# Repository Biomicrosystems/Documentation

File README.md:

# Logos
- The Logo of our group, and all of its versions, has been developed by Designer and Electronic Engineer Gina Paola Salazar

# Figures for papers, presentations, thesis and posters
- All figures of equipment and microsystems were produced by Designer Maria Alejandra Mariño 

When using these images please acknowledge respectively

# File Formats
- LABBOOK: The Excel file format of our groups to document your experimental data
- Confidential Agreement (NDA): document to sign the confidential agreement of the group (spanish version)
- Poster: Our group's powerpoint format for posters
- Presentation: Our group's powerpoint format for presentations

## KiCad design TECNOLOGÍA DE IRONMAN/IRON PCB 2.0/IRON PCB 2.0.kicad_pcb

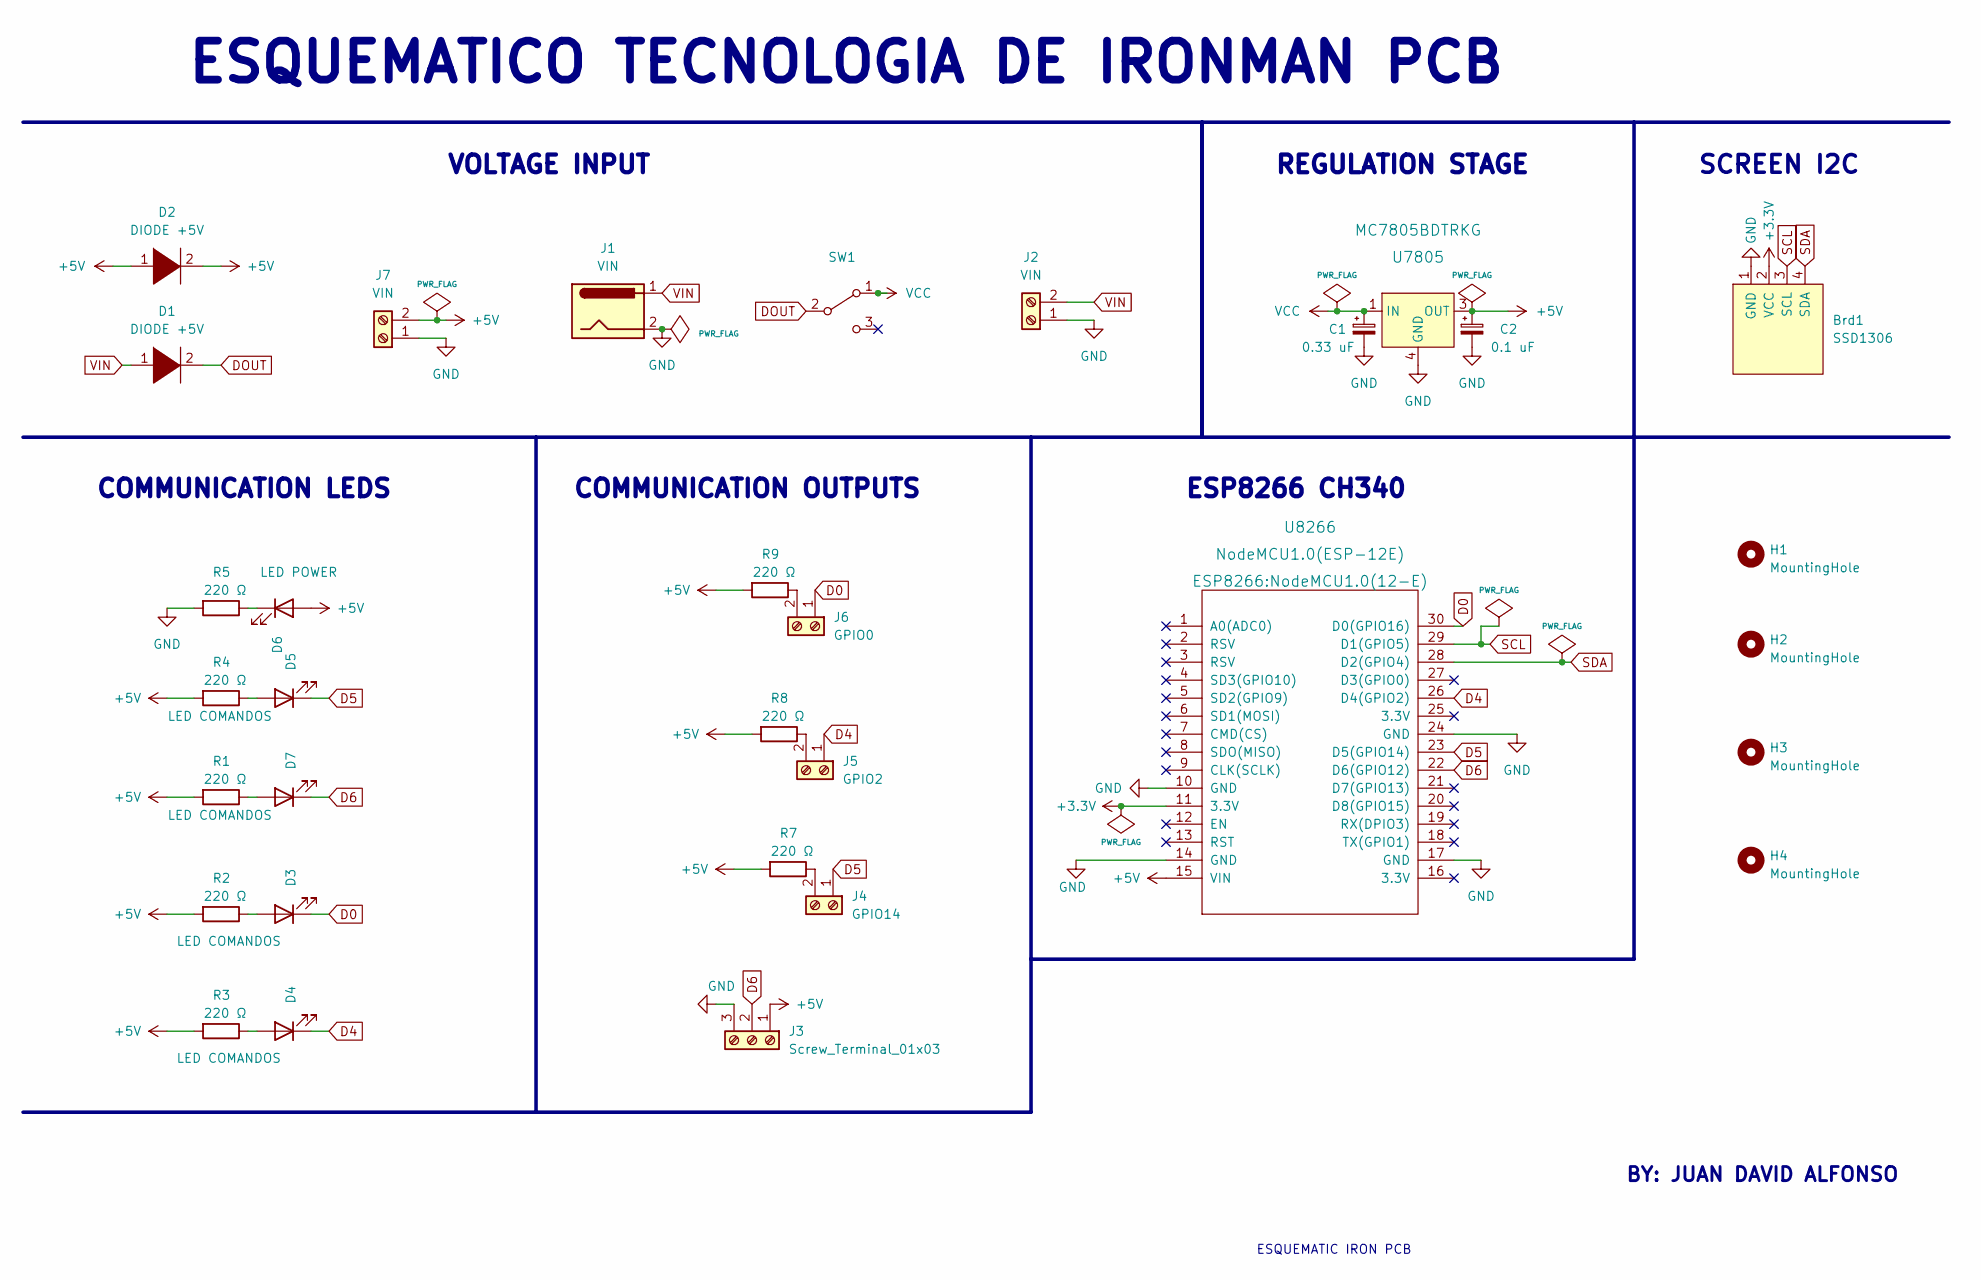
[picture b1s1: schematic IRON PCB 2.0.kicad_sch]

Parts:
Brd1: SSD1306; OLED
C1: 0.33 uF; CP_Elec_5x5.9
C2: 0.1 uF; CP_Elec_5x5.9
D1, D2: DIODE +5V; DO-214AC
D3, D4, D5: LED COMANDOS; LED_D3.0mm
D6: LED POWER; LED_D3.0mm
D7: LED COMANDOS; LED_D3.0mm_FlatTop
H1, H2, H3, H4: MountingHole; MountingHole_3.2mm_M3_Pad_Via
J1: VIN; BarrelJack_CUI_PJ-102AH_Horizontal
J2, J7: VIN; TerminalBlock_Phoenix_MKDS-1,5-2_1x02_P5.00mm_Horizontal
J3: Screw_Terminal_01x03; TerminalBlock_Phoenix_MKDS-1,5-3_1x03_P5.00mm_Horizontal
J4: GPIO14; TerminalBlock_Phoenix_MKDS-1,5-2_1x02_P5.00mm_Horizontal
J5: GPIO2; TerminalBlock_Phoenix_MKDS-1,5-2_1x02_P5.00mm_Horizontal
J6: GPIO0; TerminalBlock_Phoenix_MKDS-1,5-2_1x02_P5.00mm_Horizontal
R1, R2, R3, R4, R5, R7, R8, R9: 220 Ω; R_1206_3216Metric
SW1: SWICH; PinHeader_1x03_P2.54mm_Vertical
U7805: MC7805BDTRKG; TO-252-3; MPN MC7805BDTRKG; Digi-Key_PN MC7805BDTRKGOSCT-ND
U8266: NodeMCU1.0(ESP-12E); NodeMCU1.0(12-E)

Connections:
+3.3V: Brd1.2 (VCC), U8266.11 (3.3V)
+5V: C2.1, D2.1 (K), D2.2 (A), D6.2 (A), J3.1, J7.2, R1.2, R2.2, R3.2, R4.2, R7.2, R8.2, R9.2, U7805.3 (OUT), U8266.15 (VIN)
D0: D3.1 (K), J6.1, U8266.30 (D0(GPIO16))
D4: D4.1 (K), J5.1, U8266.26 (D4(GPIO2))
D5: D5.1 (K), J4.1, U8266.23 (D5(GPIO14))
D6: D7.1 (K), J3.2, U8266.22 (D6(GPIO12))
DOUT: D1.2 (A), SW1.2 (B)
GND: Brd1.1 (GND), C1.2, C2.2, J1.2, J2.1, J3.3, J7.1, R5.2, U7805.4 (GND), U8266.10 (GND), U8266.14 (GND), U8266.17 (GND), U8266.24 (GND)
unnamed: D3.2 (A), R2.1
unnamed: D4.2 (A), R3.1
unnamed: D5.2 (A), R4.1
unnamed: D6.1 (K), R5.1
unnamed: D7.2 (A), R1.1
unnamed: J4.2, R7.1
unnamed: J5.2, R8.1
unnamed: J6.2, R9.1
SCL: Brd1.3 (SCL), U8266.29 (D1(GPIO5))
SDA: Brd1.4 (SDA), U8266.28 (D2(GPIO4))
VCC: C1.1, SW1.1 (A), U7805.1 (IN)
VIN: D1.1 (K), J1.1, J2.2

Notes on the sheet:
ESQUEMATICO TECNOLOGIA DE IRONMAN PCB
COMMUNICATION OUTPUTS
SCREEN I2C
ESQUEMATIC IRON PCB
VOLTAGE INPUT
ESP8266 CH340
REGULATION STAGE
COMMUNICATION LEDS
BY: JUAN DAVID ALFONSO

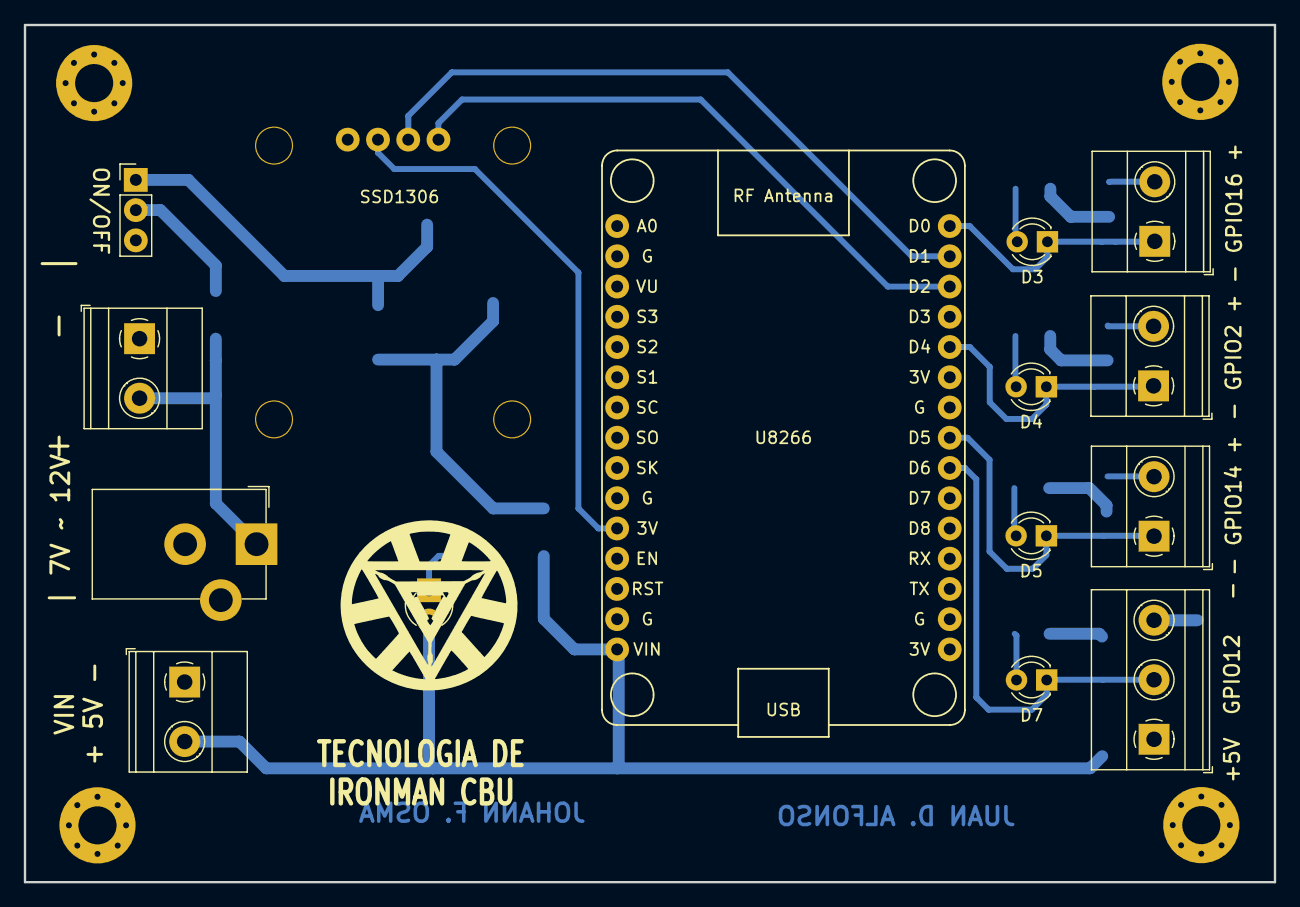
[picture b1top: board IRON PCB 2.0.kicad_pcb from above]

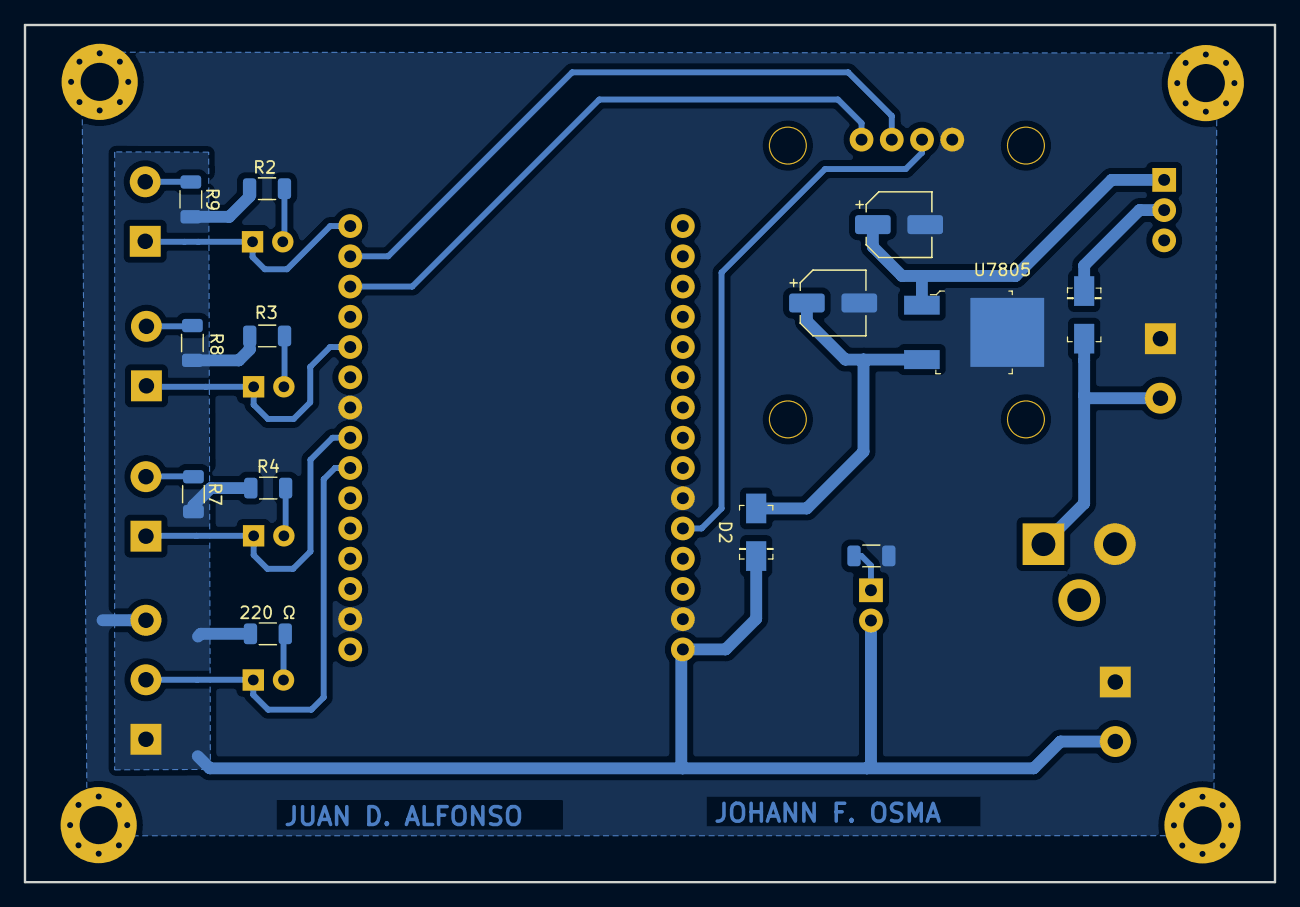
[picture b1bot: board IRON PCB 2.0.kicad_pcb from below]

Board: 2 copper layers, 105.0 x 72.0 mm, 32 parts (13 on the bottom side), 20 nets.

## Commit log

2022-04-19 add VS gitignore
2022-04-19 invert current value
2022-04-28 Add config json
2022-04-28 Update executable files
2022-08-20 Upgrade Installer to V 1.1.0.0
2022-08-20 Update latest pc version
    Latest Pc software is updated
2022-09-16 Documentacion uso y manejo del potenciostato
2023-01-19 Create adsfads
2023-01-19 Rename Videos.md to README.md
2023-02-01 Create gitkeep
2023-02-19 Create: Folder photos principal page biomicrosystems
2023-02-19 Update: Update photos - page biomicrosystems
2023-02-19 Update Update photos
2023-03-02 Page-web
2023-03-05 Feature: photo page areas
2023-03-05 Feature: Delete file in proyect
2023-03-05 Feature: Add proeyct in angular, pricnipal proyect
2023-03-05 Feature: Ajust logic members & styles
2023-03-06 Features: Added member cards
2023-03-16 Added Individual Photos
2023-03-16 Features: Added Members
2023-03-17 Feature: Added all I&M members
2023-03-17 Feature: Added Members to RSA
2023-03-18 Feature: Classified unassigned members
2023-03-19 Feature: Adjust button member page & navbar component
2023-03-19 Feature: Update publications page
2023-03-19 Feature: Update member Page
2023-03-19 Feature: Adjust size individual photos
2023-03-22 Added member pictures
2023-03-22 Feature: Corrections in members page
2023-03-22 Feature: Added missing active members
2023-03-23 Feature: Added members' missing information
2023-04-06 Feature: Clear Code
2023-04-06 Featute: Create carousel
2023-04-06 Feature: Folder carousel photos
2023-04-06 Feature: Adjust Carousel
2023-04-12 Feature: Added ALL pending graduate members
2023-04-12 Fixed cards with missing info
2023-04-13 Feature: Adjust responsive page
2023-04-13 Feature: Adjust responsive footer
2023-04-14 Arreglos página
2023-04-14 Feature: minor corrections
2023-04-17 PAWL-CLIENT
    Aqui se encontrará el código fuente con el que debe ser programado el microcontrolador
2023-04-17 PAWL-UI
    Aquí se muestra la interfaz gradica de PAWL
2023-04-17 PAWL-UI
    Aquí se muestra el código relacionado con la API del sistema
2023-04-27 Feature: Uodate carousel in principal-page
2023-06-26 Feature: Update page
2023-06-26 Update: Update page biomicrosuystem
2023-06-26 Update: delete comment
2023-06-26 Feature: Adjust styles footer
2023-06-26 Feature: Adjust page
2023-06-26 Feature: Fixed members photos and footer grammar
2023-06-27 Feature: Update footer & index, in page.
2023-06-29 Feature: Files dockerization image project
2023-07-06 Add files via upload
    Este archivo presenta la versión final del programa de arduino IDE para controlar el robot a través de un microcontrolador Nodemcu basado en ESP8266.
2024-01-29 Bomba jeringa para microfluidica
2024-09-24 Documentacíon CBU IronMan
2024-09-25 IRON APK
